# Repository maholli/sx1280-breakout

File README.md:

# sx1280-breakout
breakout board for Semtech SX1280 LoRa radio compatible with RFM9x footprints

 - [ ] TODO: add cleverly-optional U.FL to antenna signal path

## [Schematic (PDF)](SX1280-breakout.pdf)

## Stack up
Assuming Isola FR408
 - layer 1 1.7mils 1oz Cu
 - 7.5 mils prepreg
 - layer 2 1.4 mils 1oz Cu
 - 40 mils core
 - layer 3 1.4 mils 1oz Cu
 - 7.5 mils prepreg
 - layer 4 1.7mils 1oz Cu

For coplanar wave guide with ground plane:
 - 50 ohm at 2.4G = 7.65 mils trace width with spacing of 5 mils.

# KiKit Panelize
```bash
kikit panelize \
    --layout 'alternation: cols; hspace: 2.4mm; vspace: 2.4mm; cols: 4' \
    --source 'tolerance: 15mm' \
    --tabs 'type: annotation' \
    --cuts 'type: mousebites; offset: -0.1mm' \
    --framing 'type: railstb; vspace: 2.4mm; width: 3mm' \
    --fiducials 'type: 3fid; hoffset: 1.5mm; voffset: 1.5mm; opening: 2mm' \
    --post 'millradius: 1.2mm; origin: bl' \
    \GitHub\sx1280-breakout\SX1280-breakout.kicad_pcb panel.kicad_pcb
```

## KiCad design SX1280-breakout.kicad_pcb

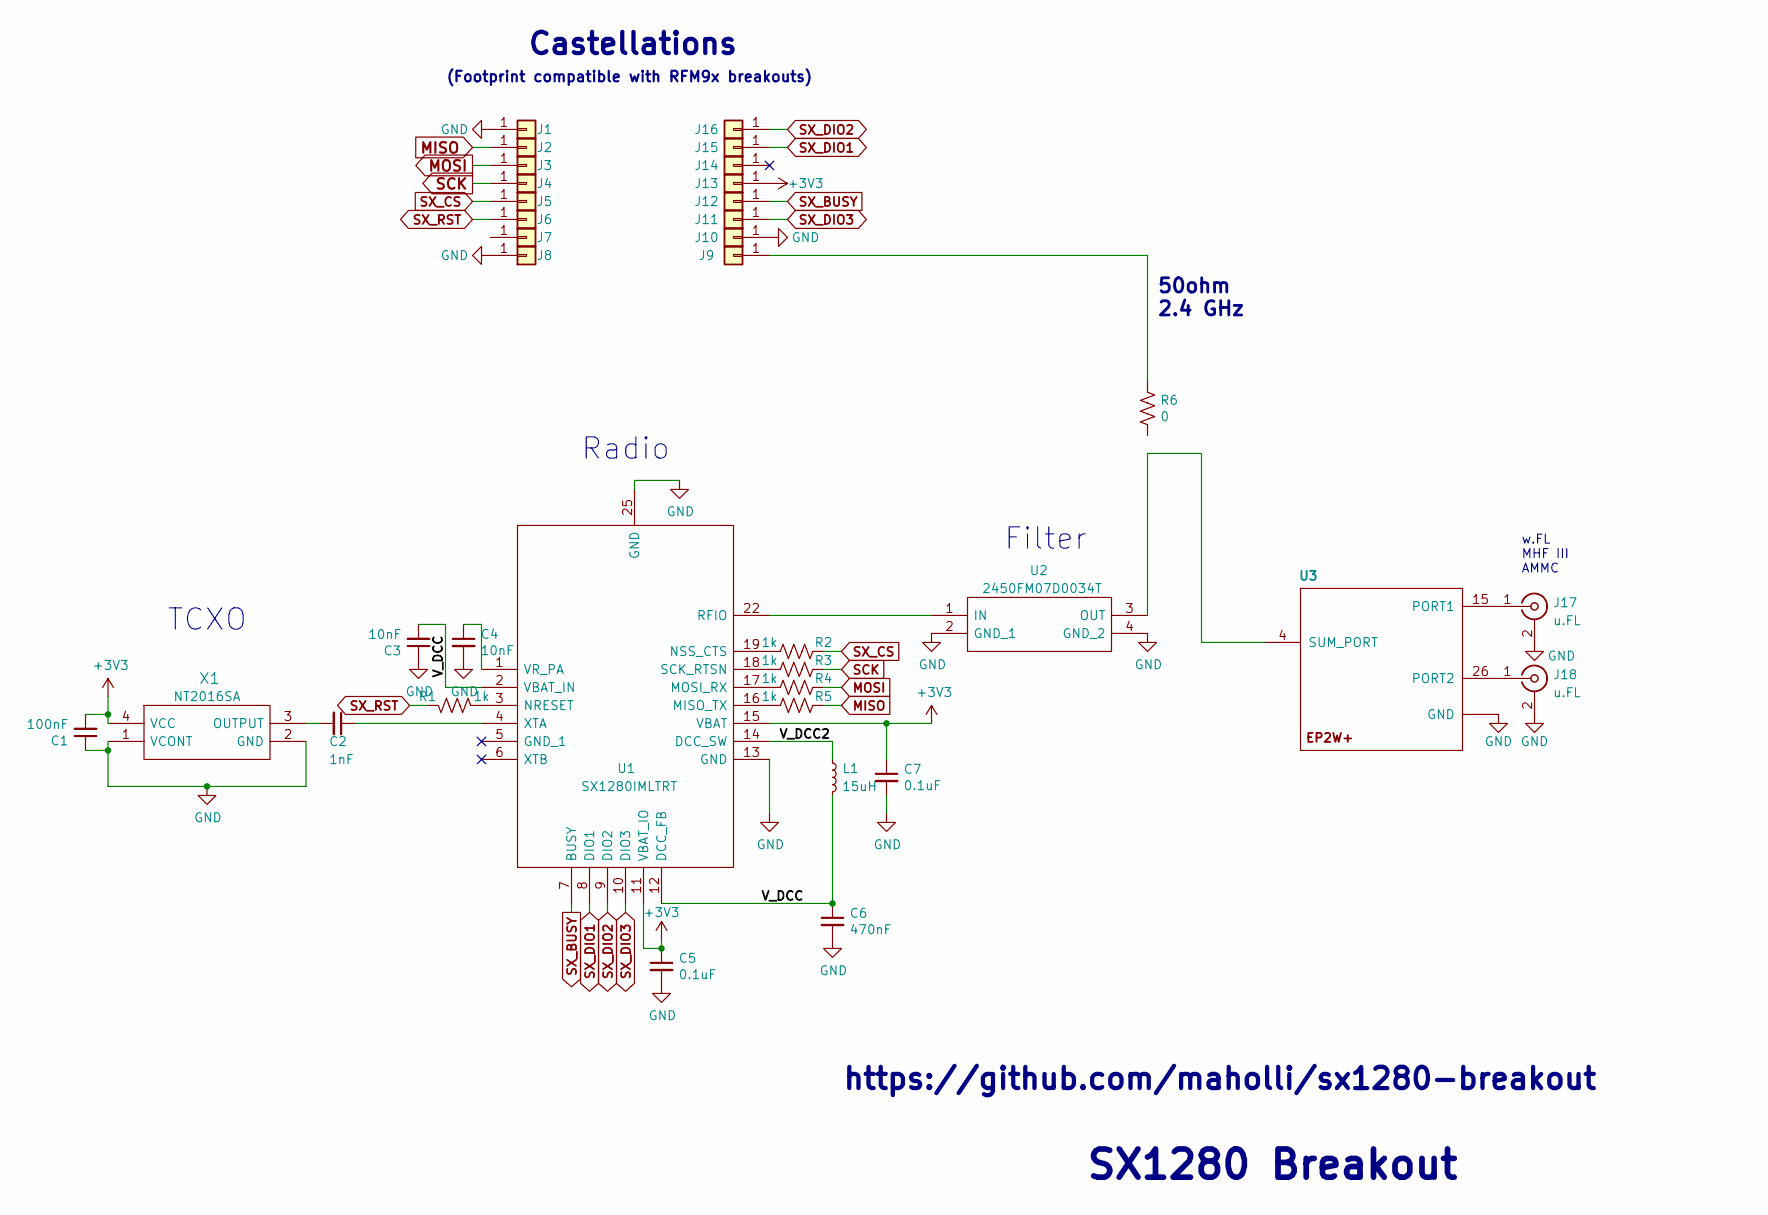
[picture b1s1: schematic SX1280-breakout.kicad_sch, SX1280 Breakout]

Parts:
C1: 100nF; C_0402_1005Metric
C2: 1nF; C_0402_1005Metric
C3, C4: 10nF; C_0402_1005Metric
C5, C7: 0.1uF; C_0402_1005Metric
C6: 470nF; C_0402_1005Metric
J1, J2, J3, J4, J5, J6, J7, J8, J9, J10, J11, J12, J13, J14, J15, J16: Conn_01x01; castellated_04mm
J17, J18: u.FL; U.FL_Hirose_U.FL-R-SMT-1_Vertical
L1: 15uH; L_0805_2012Metric
R1, R2, R3, R4, R5: 1k; R_0402_1005Metric
R6: 0; R_0201_0603Metric
U1: SX1280IMLTRT; QFN50P400X400X80-25N-D; Manufacturer_Part_Number SX1280IMLTRT; Mouser Part Number 947-SX1280IMLTRT
U2: 2450FM07D0034T; Manufacturer_Part_Number 2450FM07D0034T; Mouser Part Number 609-2450FM07D0034T
U3: EP2W+; QFN32-5X5MM; Manufacturer_Part_Number EP2W+
X1: 52.000 MHz; Crystal_SMD_2016-4Pin_2.0x1.6mm; Manufacturer_Part_Number NT2016SA-38.4MHZ-END4679A

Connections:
+3V3: C1.2, C5.1, C7.1, J13.1, U1.11 (VBAT_IO), U1.15 (VBAT), X1.4 (VCC)
/V_DCC: C3.2, C6.1, L1.2, U1.2 (VBAT_IN), U1.12 (DCC_FB)
/V_DCC2: L1.1, U1.14 (DCC_SW)
GND: C1.1, C3.1, C4.2, C5.2, C6.2, C7.2, J1.1, J8.1, J10.1, J17.2 (Ext), J18.2 (Ext), U1.13 (GND), U1.20 (GND), U1.21 (GND), U1.23 (GND), U1.24 (GND), U1.25 (GND), U2.2 (GND_1), U2.4 (GND_2), U3.1 (GND), U3.2 (GND), U3.3 (GND), U3.5 (GND), U3.6 (GND), U3.7 (GND), U3.8 (GND), U3.9 (GND), U3.10 (GND), U3.11 (GND), U3.12 (GND), U3.13 (GND), U3.14 (GND), U3.16 (GND), U3.17 (GND), U3.18 (GND), U3.19 (GND), U3.20 (GND), U3.21 (GND), U3.22 (GND), U3.23 (GND), U3.24 (GND), U3.25 (GND), U3.27 (GND), U3.28 (GND), U3.29 (GND), U3.30 (GND), U3.31 (GND), U3.32 (GND), U3.EP (GND), X1.1 (VCONT), X1.2 (GND)
MISO: J2.1, R5.1
MOSI: J3.1, R4.1
unnamed: C2.1, U1.4 (XTA)
unnamed: C2.2, X1.3 (OUTPUT)
unnamed: C4.1, U1.1 (VR_PA)
unnamed: J9.1, R6.2
unnamed: J17.1 (In), U3.15 (PORT1)
unnamed: J18.1 (In), U3.26 (PORT2)
unnamed: R1.2, U1.3 (NRESET)
unnamed: R2.2, U1.19 (NSS_CTS)
unnamed: R3.2, U1.18 (SCK_RTSN)
unnamed: R4.2, U1.17 (MOSI_RX)
unnamed: R5.2, U1.16 (MISO_TX)
unnamed: U1.22 (RFIO), U2.1 (IN)
unnamed: U2.3 (OUT), U3.4 (SUM_PORT)
SCK: J4.1, R3.1
SX_BUSY: J12.1, U1.7 (BUSY)
SX_CS: J5.1, R2.1
SX_DIO1: J15.1, U1.8 (DIO1)
SX_DIO2: J16.1, U1.9 (DIO2)
SX_DIO3: J11.1, U1.10 (DIO3)
SX_RST: J6.1, R1.1

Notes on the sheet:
https://github.com/maholli/sx1280-breakout
TCXO
Castellations
SX1280 Breakout
w.FL MHF III AMMC
Filter
Radio
(Footprint compatible with RFM9x breakouts)
50ohm 2.4 GHz

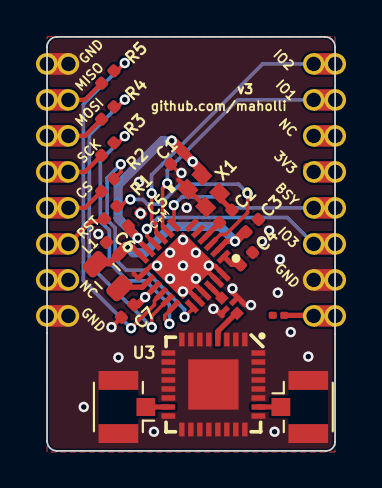
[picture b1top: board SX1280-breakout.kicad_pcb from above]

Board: 4 copper layers, 16.0 x 23.0 mm, 37 parts (0 on the bottom side), 26 nets.

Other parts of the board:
Ref**: Val**; holliday

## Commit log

2019-06-30 adding layout files
2019-06-30 adding board pic
2019-06-30 linking to schematic
2019-06-30 fix pic
2019-07-01 updating padstacks
2019-08-12 fixing TCXO cap
2019-10-16 Making PN visible on schematic PDF
2019-11-02 interactive BOM
2022-01-03 updating to v2
2022-05-15 playing with inline RF connector + updating to KiCad6
2022-05-15 gitignore
2022-05-15 removing old kicad5
2022-05-15 git ignore
2022-05-15 switched to 0.4mm castellations & routed
2022-05-16 generated kikit panel
2022-05-22 changed to u.FL (undecided)
2022-05-22 panelized just in case
2022-09-27 back to single antenna
